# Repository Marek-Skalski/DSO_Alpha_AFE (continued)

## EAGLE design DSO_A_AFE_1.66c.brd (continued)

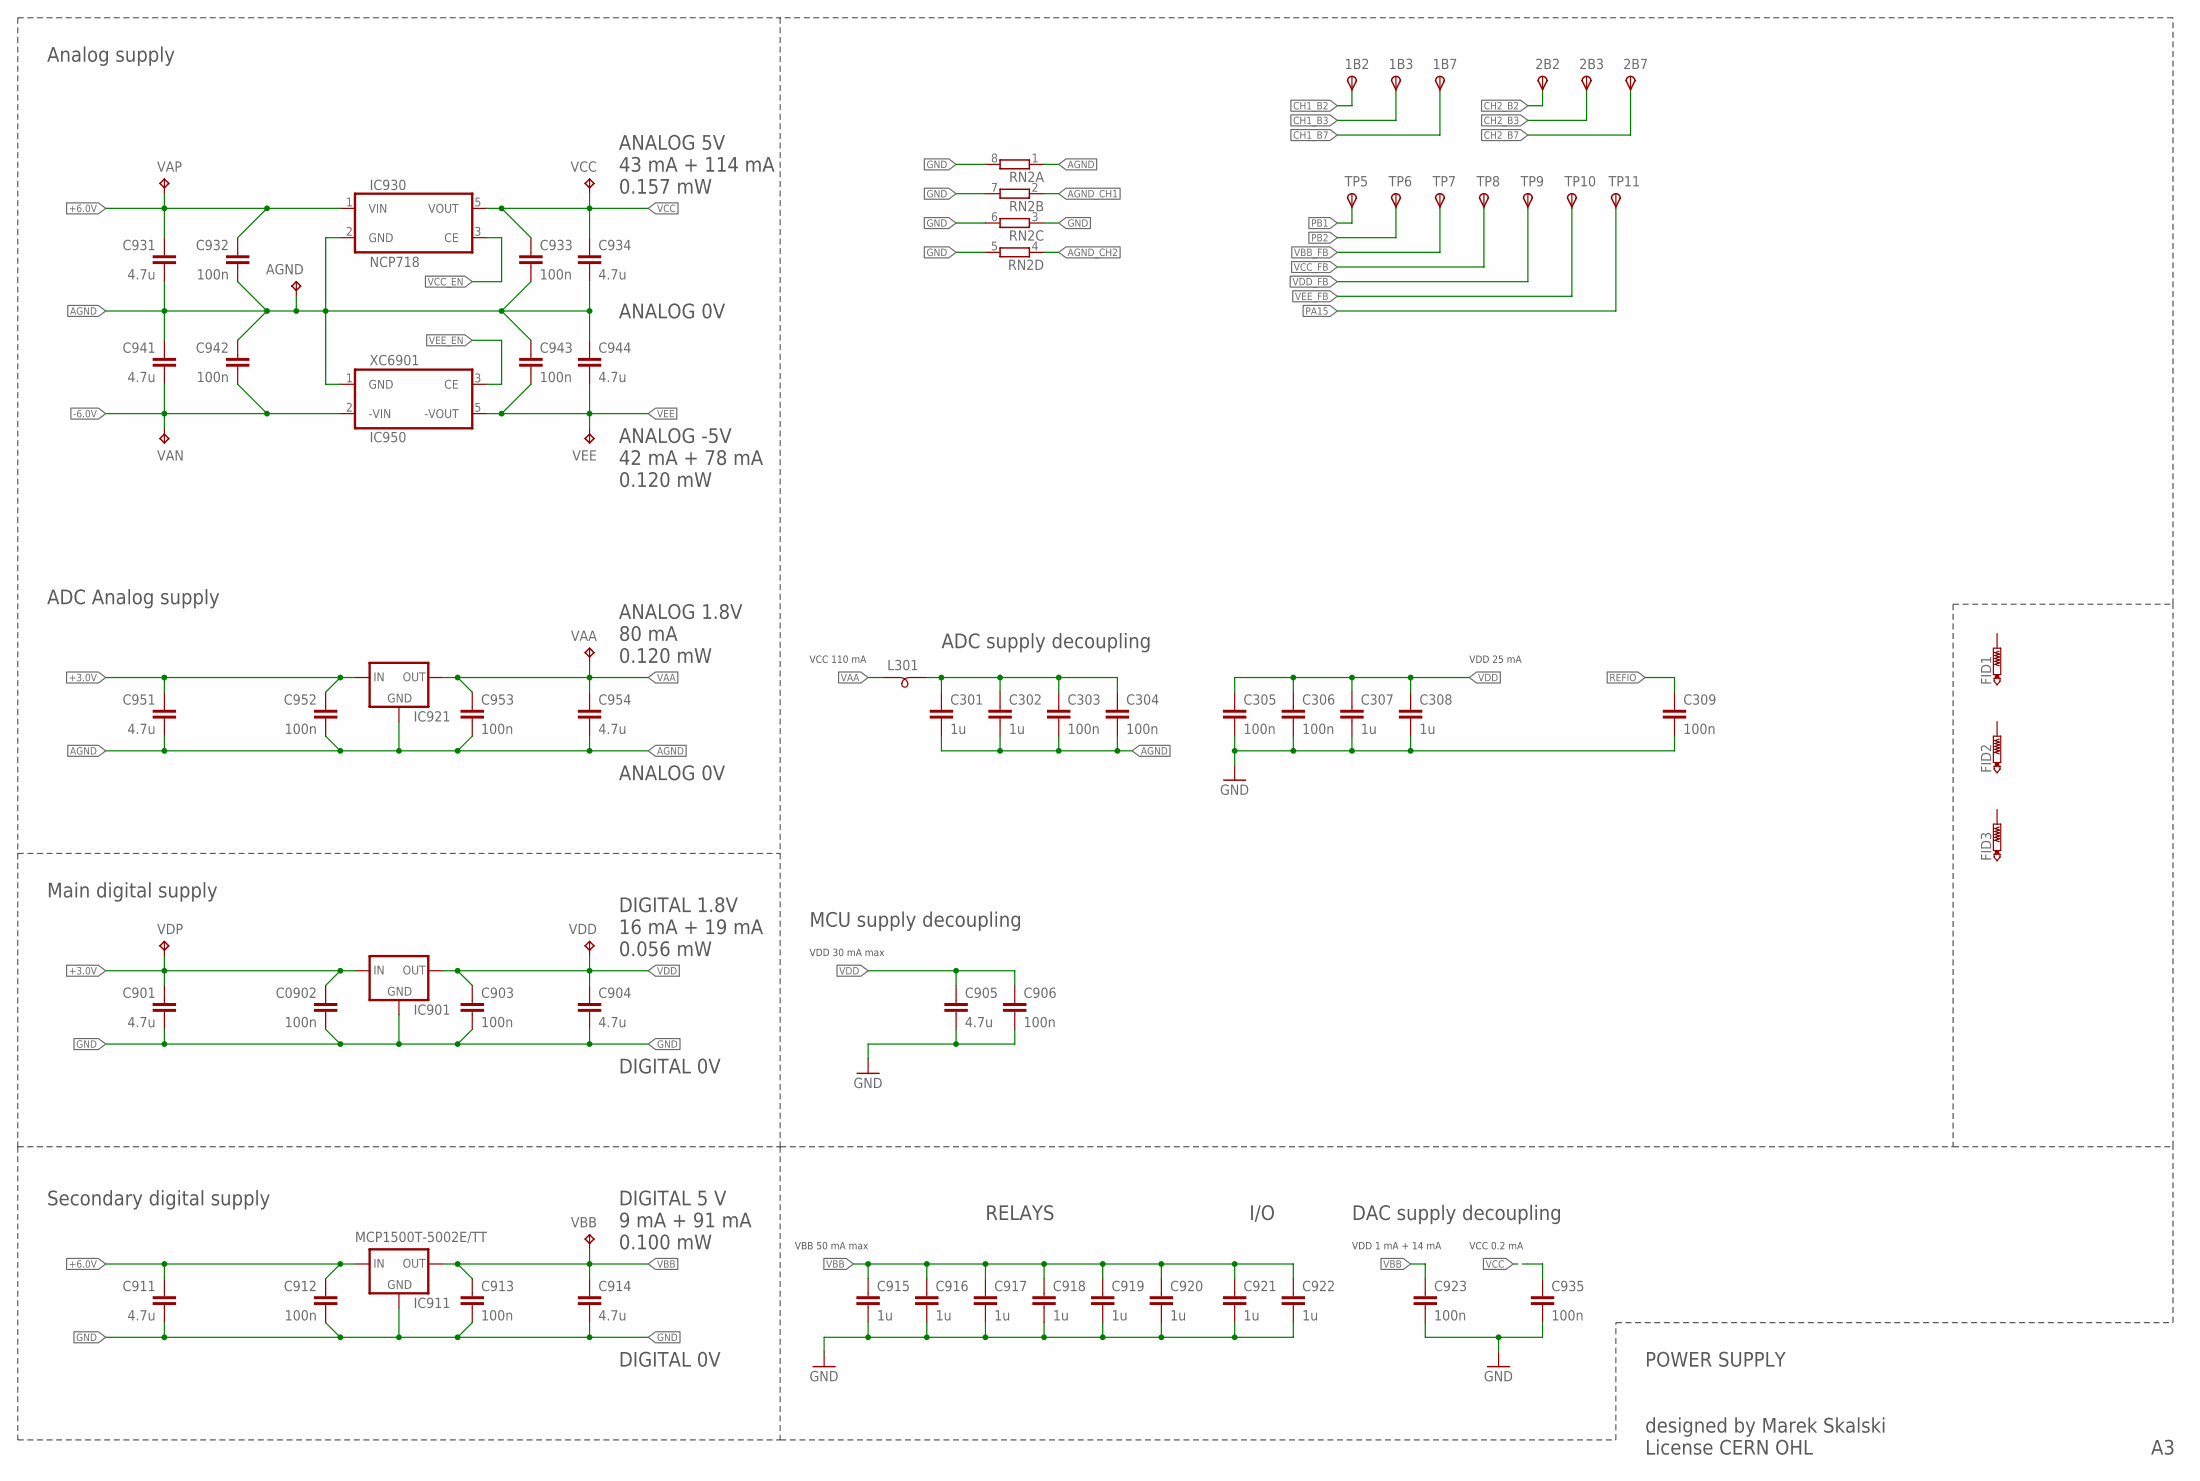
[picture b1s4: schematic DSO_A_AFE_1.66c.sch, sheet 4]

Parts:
1B2, 1B3, 1B7, 2B2, 2B3, 2B7: TPSTP10R; TP10R
AGND: TPB1,27; B1,27
C301, C302, C307, C308, C915, C916, C917, C918, C919, C920, C921, C922: 1u; C0603
C303, C304, C305, C306, C309, C0902, C903, C906, C912, C913, C923, C932, C933, C935, C942, C943, C952, C953: 100n; C0603
C901, C904, C905, C911, C914, C931, C934, C941, C944, C951, C954: 4.7u; C0603
FID1, FID2, FID3: PTR1TP07SQ; TP07SQ
IC901, IC921: MCP1500; SOT23
IC911: MCP1500T-5002E/TT; SOT23
IC930: NCP718; SOT25
IC950: XC6901; SOT25
L301: SM-B0603; 0603
RN2: 4R-N0603-ARC; 0603-ARC
TP5, TP6, TP7, TP8, TP9, TP10, TP11: TPSTP10R; TP10R
VAA: TPB1,27; B1,27
VAN: TPB1,27; B1,27
VAP: TPB1,27; B1,27
VBB: TPB1,27; B1,27
VCC: TPB1,27; B1,27
VDD: TPB1,27; B1,27
VDP: TPB1,27; B1,27
VEE: TPB1,27; B1,27

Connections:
+3.0V: C901.1, C0902.1, C951.1, C952.1, IC901.3 (IN), IC921.3 (IN), VDP.TP; also elsewhere on the board
+6.0V: C911.1, C912.1, C931.1, C932.1, IC911.3 (IN), IC930.1 (VIN), VAP.TP; also elsewhere on the board
-6.0V: C941.2, C942.2, IC950.2 (-VIN), VAN.TP; also elsewhere on the board
AGND: AGND.TP, C301.2, C302.2, C303.2, C304.2, C931.2, C932.2, C933.2, C934.2, C941.1, C942.1, C943.1, C944.1, C951.2, C952.2, C953.2, C954.2, IC921.1 (GND), IC930.2 (GND), IC950.1 (GND), RN2.1; also elsewhere on the board
AGND_CH1: RN2.2 (1); also elsewhere on the board
AGND_CH2: RN2.4 (1); also elsewhere on the board
CH1_B2: 1B2.TP; also elsewhere on the board
CH1_B3: 1B3.TP; also elsewhere on the board
CH1_B7: 1B7.TP; also elsewhere on the board
CH2_B2: 2B2.TP; also elsewhere on the board
CH2_B3: 2B3.TP; also elsewhere on the board
CH2_B7: 2B7.TP; also elsewhere on the board
GND: C305.2, C306.2, C307.2, C308.2, C309.2, C901.2, C0902.2, C903.2, C904.2, C905.2, C906.2, C911.2, C912.2, C913.2, C914.2, C915.2, C916.2, C917.2, C918.2, C919.2, C920.2, C921.2, C922.2, C923.2, C935.2, IC901.1 (GND), IC911.1 (GND), RN2.3 (1), RN2.5 (2), RN2.6 (2), RN2.7 (2), RN2.8 (2); also elsewhere on the board
PA15: TP11.TP; also elsewhere on the board
PB1: TP5.TP; also elsewhere on the board
PB2: TP6.TP; also elsewhere on the board
REFIO: C309.1; also elsewhere on the board
VAA: C953.1, C954.1, IC921.2 (OUT), L301.1, VAA.TP
VAA1: C301.1, C302.1, C303.1, C304.1, L301.2; also elsewhere on the board
VBB: C913.1, C914.1, C915.1, C916.1, C917.1, C918.1, C919.1, C920.1, C921.1, C922.1, C923.1, IC911.2 (OUT), VBB.TP; also elsewhere on the board
VBB_FB: TP7.TP; also elsewhere on the board
VCC: C933.1, C934.1, C935.1, IC930.5 (VOUT), VCC.TP; also elsewhere on the board
VCC_EN: IC930.3 (CE); also elsewhere on the board
VCC_FB: TP8.TP; also elsewhere on the board
VDD: C305.1, C306.1, C307.1, C308.1, C903.1, C904.1, C905.1, C906.1, IC901.2 (OUT), VDD.TP; also elsewhere on the board
VDD_FB: TP9.TP; also elsewhere on the board
VEE: C943.2, C944.2, IC950.5 (-VOUT), VEE.TP; also elsewhere on the board
VEE_EN: IC950.3 (CE); also elsewhere on the board
VEE_FB: TP10.TP; also elsewhere on the board

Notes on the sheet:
POWER SUPPLY designed by Marek Skalski License CERN OHL
DIGITAL 1.8V 16 mA + 19 mA 0.056 mW
DIGITAL 5 V 9 mA + 91 mA 0.100 mW
DIGITAL 0V
ANALOG 0V
ANALOG 5V 43 mA + 114 mA 0.157 mW
ANALOG -5V 42 mA + 78 mA 0.120 mW
DAC supply decoupling
ADC supply decoupling
MCU supply decoupling
RELAYS
VDD 1 mA + 14 mA
VCC 0.2 mA
VCC 110 mA
VDD 25 mA
VDD 30 mA max
VBB 50 mA max
Analog supply
Main digital supply
Secondary digital supply
ANALOG 1.8V 80 mA 0.120 mW
ADC Analog supply
I/O

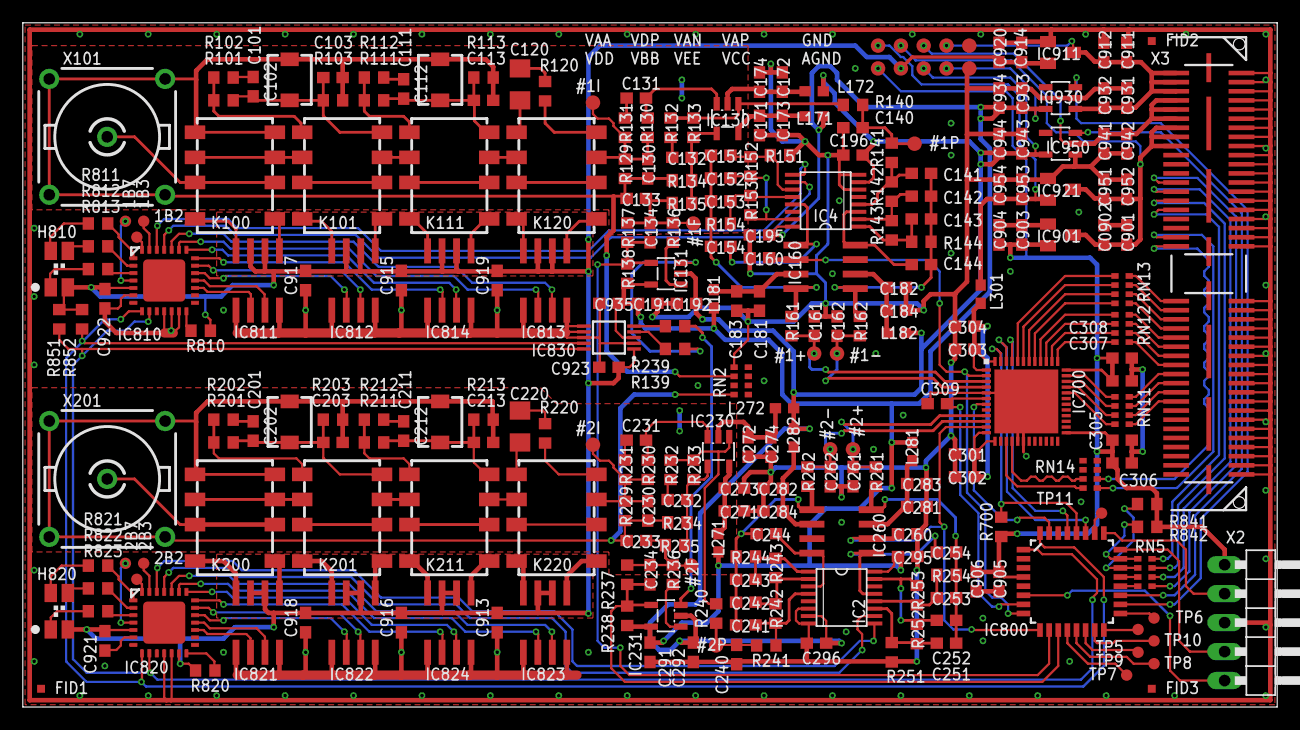
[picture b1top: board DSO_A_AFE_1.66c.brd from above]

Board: 2 copper layers, 110.0 x 60.0 mm, 275 parts (0 on the bottom side), 214 nets.
